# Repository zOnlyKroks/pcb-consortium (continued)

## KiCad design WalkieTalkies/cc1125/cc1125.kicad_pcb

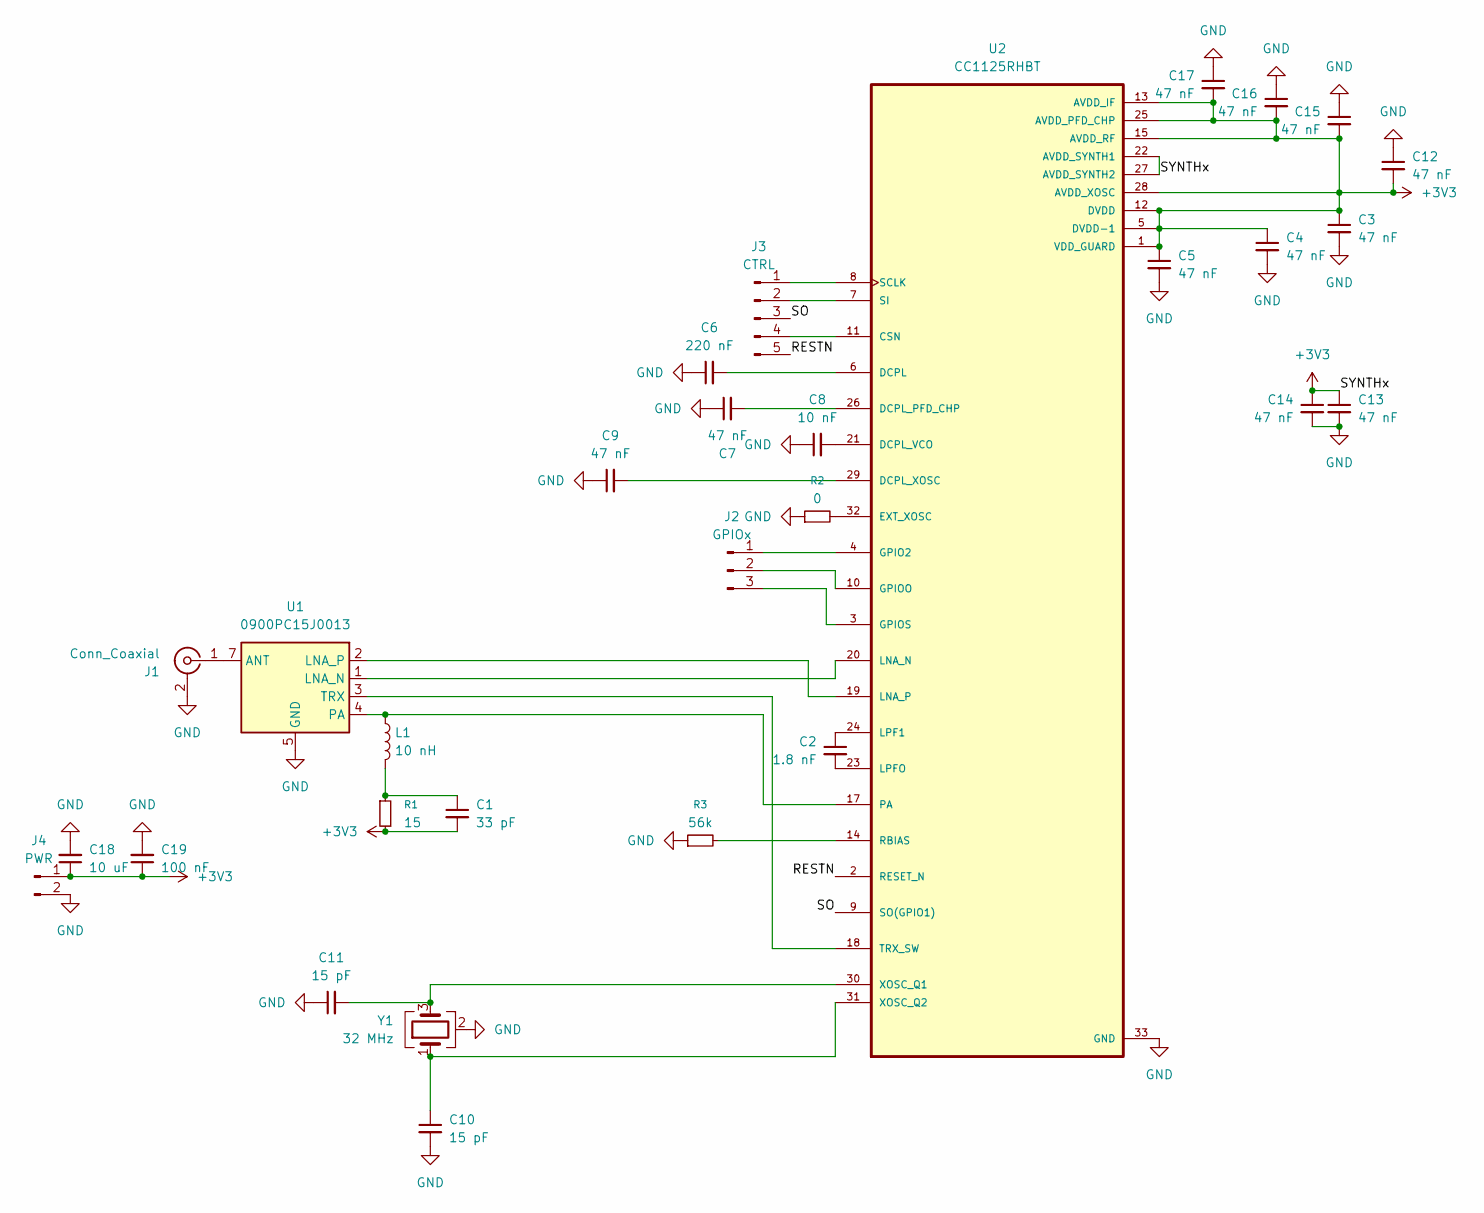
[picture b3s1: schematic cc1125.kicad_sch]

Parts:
C1: 33 pF; C_0603_1608Metric
C2: 1.8 nF; C_0603_1608Metric
C3, C4, C5, C7, C9, C12, C13, C14, C15, C16, C17: 47 nF; C_0603_1608Metric
C6: 220 nF; C_0603_1608Metric
C8: 10 nF; C_0603_1608Metric
C10, C11: 15 pF; C_0603_1608Metric
C18: 10 uF; C_0603_1608Metric
C19: 100 nF; C_0603_1608Metric
J1: Conn_Coaxial; SMA_BAT_Wireless_BWSMA-KWE-Z001
J2: GPIOx; PinHeader_1x03_P2.54mm_Vertical
J3: CTRL; PinHeader_1x05_P2.54mm_Vertical
J4: PWR; PinHeader_1x02_P2.54mm_Vertical
L1: 10 nH; L_0805_2012Metric
R1: 15; R_0603_1608Metric
R2: 0; R_0603_1608Metric
R3: 56k; R_0603_1608Metric
U1: 0900PC15J0013; Balun_Johanson_0900PC15J0013
U2: CC1125RHBT; IC_ADS125H01IRHBT
Y1: 32 MHz; Crystal_SMD_3225-4Pin_3.2x2.5mm

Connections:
+3V3: C1.2, C3.1, C4.1, C5.1, C12.2, C13.1, C14.1, C15.2, C16.2, C17.2, C18.1, C19.1, J4.1, R1.2, U2.1 (VDD_GUARD), U2.5 (DVDD-1), U2.12 (DVDD), U2.13 (AVDD_IF), U2.15 (AVDD_RF), U2.22 (AVDD_SYNTH1), U2.25 (AVDD_PFD_CHP), U2.27 (AVDD_SYNTH2), U2.28 (AVDD_XOSC)
/RESTN: J3.5, U2.2 (RESET_N)
/SO: J3.3, U2.9 (SO(GPIO1))
GND: C3.2, C4.2, C5.2, C6.1, C7.1, C8.1, C9.1, C10.2, C11.1, C12.1, C13.2, C14.2, C15.1, C16.1, C17.1, C18.2, C19.2, J1.2 (Ext), J4.2, R2.1, R3.1, U1.5 (GND), U1.6 (GND), U1.8 (GND), U1.9 (GND), U1.10 (GND), U2.33 (GND), Y1.2 (G), Y1.4 (G)
unnamed: C1.1, L1.2, R1.1
unnamed: J1.1 (In), U1.7 (ANT)
unnamed: J2.1, U2.4 (GPIO2)
unnamed: J2.2, U2.10 (GPIOO)
unnamed: J2.3, U2.3 (GPIOS)
unnamed: J3.1, U2.8 (SCLK)
unnamed: J3.2, U2.7 (SI)
unnamed: J3.4, U2.11 (CSN)
unnamed: U1.1 (LNA_N), U2.20 (LNA_N)
unnamed: U1.2 (LNA_P), U2.19 (LNA_P)
unnamed: L1.1, U1.4 (PA), U2.17 (PA)
unnamed: U1.3 (TRX), U2.18 (TRX_SW)
unnamed: C6.2, U2.6 (DCPL)
unnamed: C7.2, U2.26 (DCPL_PFD_CHP)
unnamed: C8.2, U2.21 (DCPL_VCO)
unnamed: C9.2, U2.29 (DCPL_XOSC)
unnamed: R2.2, U2.32 (EXT_XOSC)
unnamed: C2.1, U2.24 (LPF1)
unnamed: C2.2, U2.23 (LPFO)
unnamed: R3.2, U2.14 (RBIAS)
unnamed: C11.2, U2.30 (XOSC_Q1), Y1.3
unnamed: C10.1, U2.31 (XOSC_Q2), Y1.1

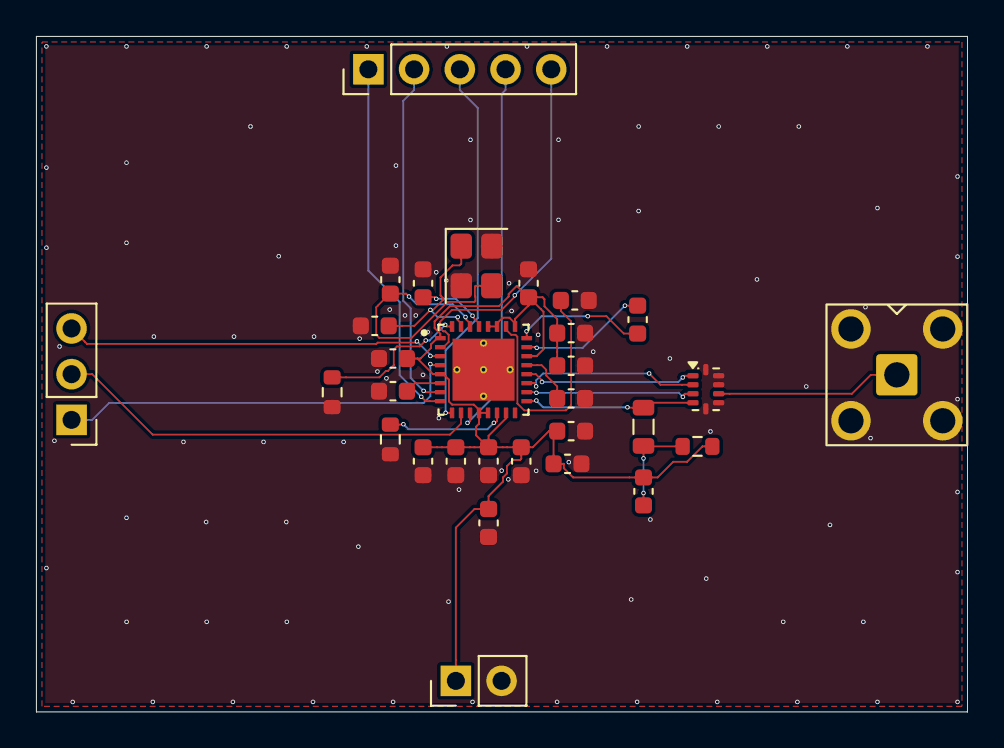
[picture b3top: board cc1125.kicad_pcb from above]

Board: 2 copper layers, 51.7 x 37.5 mm, 30 parts (0 on the bottom side), 26 nets.

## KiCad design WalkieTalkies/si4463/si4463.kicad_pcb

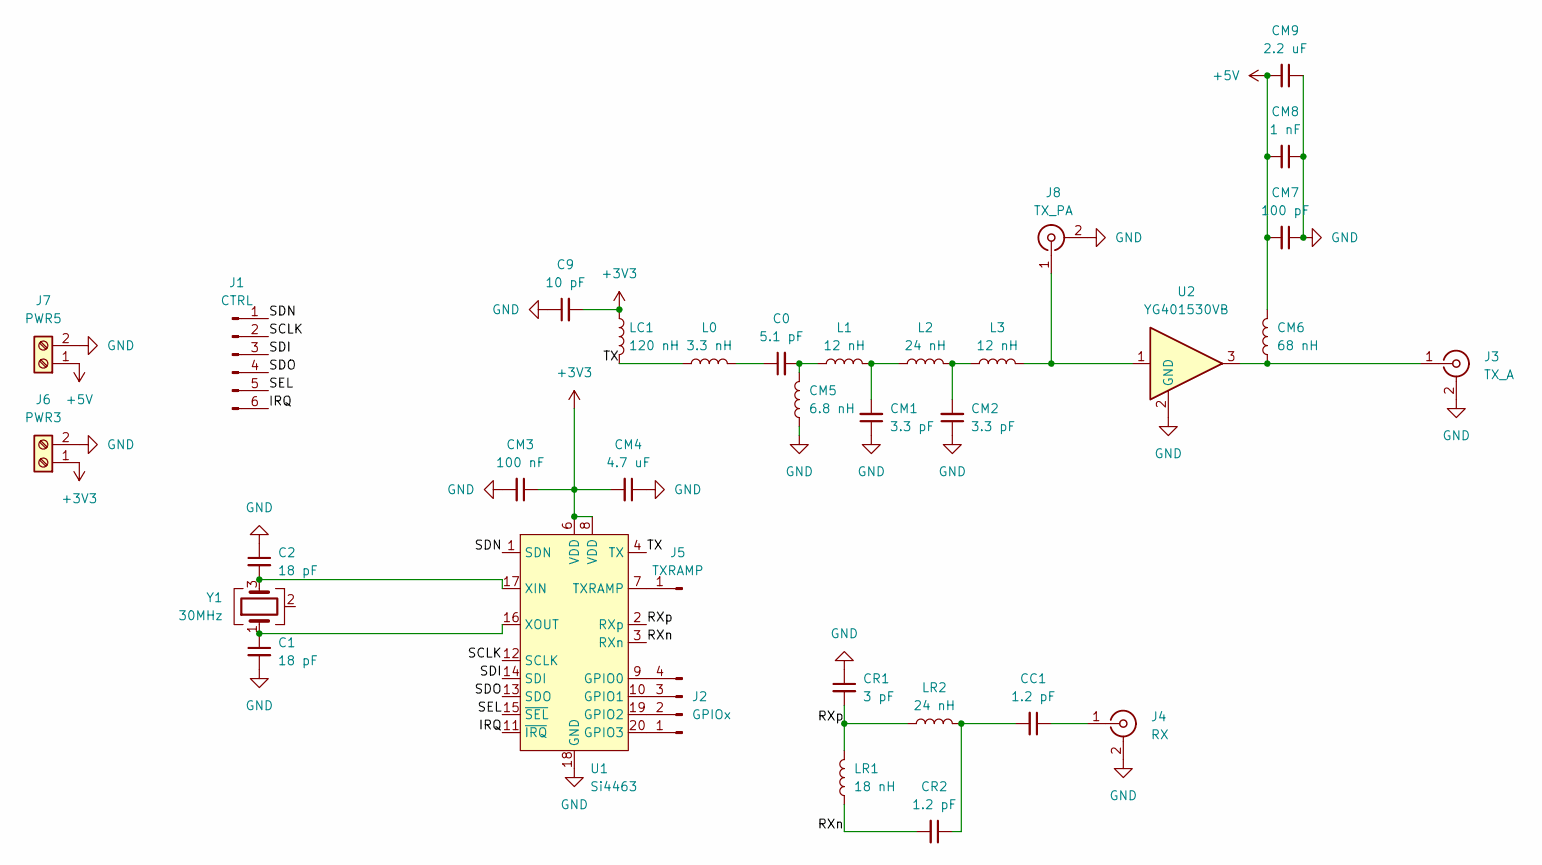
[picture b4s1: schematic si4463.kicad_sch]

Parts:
C0: 5.1 pF; C_0603_1608Metric
C1, C2: 18 pF; C_0603_1608Metric
C9: 10 pF; C_0603_1608Metric
CC1: 1.2 pF; C_0603_1608Metric
CM1, CM2: 3.3 pF; C_0603_1608Metric
CM3: 100 nF; C_0603_1608Metric
CM4: 4.7 uF; C_0603_1608Metric
CM5: 6.8 nH; L_0805_2012Metric
CM6: 68 nH; L_0805_2012Metric
CM7: 100 pF; C_0603_1608Metric
CM8: 1 nF; C_0603_1608Metric
CM9: 2.2 uF; C_0603_1608Metric
CR1: 3 pF; C_0603_1608Metric
CR2: 1.2 pF; C_0603_1608Metric
J1: CTRL; PinHeader_1x06_P2.54mm_Vertical
J2: GPIOx; PinHeader_1x04_P2.54mm_Vertical
J3: TX_A; SMA_BAT_Wireless_BWSMA-KWE-Z001
J4: RX; SMA_BAT_Wireless_BWSMA-KWE-Z001
J5: TXRAMP; PinHeader_1x01_P2.54mm_Vertical
J6: PWR3; WJ500V-5.08-2P
J7: PWR5; WJ500V-5.08-2P
J8: TX_PA; SMA_BAT_Wireless_BWSMA-KWE-Z001
L0: 3.3 nH; L_0805_2012Metric
L1, L3: 12 nH; L_0805_2012Metric
L2: 24 nH; L_0805_2012Metric
LC1: 120 nH; L_0805_2012Metric
LR1: 18 nH; L_0805_2012Metric
LR2: 24 nH; L_0805_2012Metric
U1: Si4463; QFN-20-1EP_4x4mm_P0.5mm_EP2.6x2.6mm_ThermalVias
U2: YG401530VB; SOT-89-3
Y1: 30MHz; Crystal_SMD_3225-4Pin_3.2x2.5mm

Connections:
+3V3: C9.2, CM3.1, CM4.2, J6.1, LC1.1, U1.6 (VDD), U1.8 (VDD)
+5V: CM6.2, CM7.2, CM8.2, CM9.2, J7.1
/IRQ: J1.6, U1.11 (~IRQ)
/RXn: CR2.2, LR1.1, U1.3 (RXn)
/RXp: CR1.2, LR1.2, LR2.1, U1.2 (RXp)
/SCLK: J1.2, U1.12 (SCLK)
/SDI: J1.3, U1.14 (SDI)
/SDN: J1.1, U1.1 (SDN)
/SDO: J1.4, U1.13 (SDO)
/SEL: J1.5, U1.15 (~SEL)
/TX: L0.1, LC1.2, U1.4 (TX)
GND: C1.2, C2.1, C9.1, CM1.1, CM2.1, CM3.2, CM4.1, CM5.1, CM7.1, CM8.1, CM9.1, CR1.1, J3.2 (Ext), J4.2 (Ext), J6.2, J7.2, J8.2 (Ext), U1.18 (GND), U1.21 (GND), U2.2 (GND_2)
unnamed: C0.1, L0.2
unnamed: C0.2, CM5.2, L1.1
unnamed: CC1.2, CR2.1, LR2.2
unnamed: CM1.2, L1.2, L2.1
unnamed: CM2.2, L2.2, L3.1
unnamed: J2.1, U1.20 (GPIO3)
unnamed: J2.2, U1.19 (GPIO2)
unnamed: J2.3, U1.10 (GPIO1)
unnamed: J2.4, U1.9 (GPIO0)
unnamed: CM6.1, J3.1 (In), U2.3
unnamed: CC1.1, J4.1 (In)
unnamed: J5.1 (Pin_1_1), U1.7 (TXRAMP)
unnamed: J8.1 (In), L3.2, U2.1
unnamed: C2.2, U1.17 (XIN), Y1.3
unnamed: C1.1, U1.16 (XOUT), Y1.1
unnamed: Y1.2 (G), Y1.4 (G)

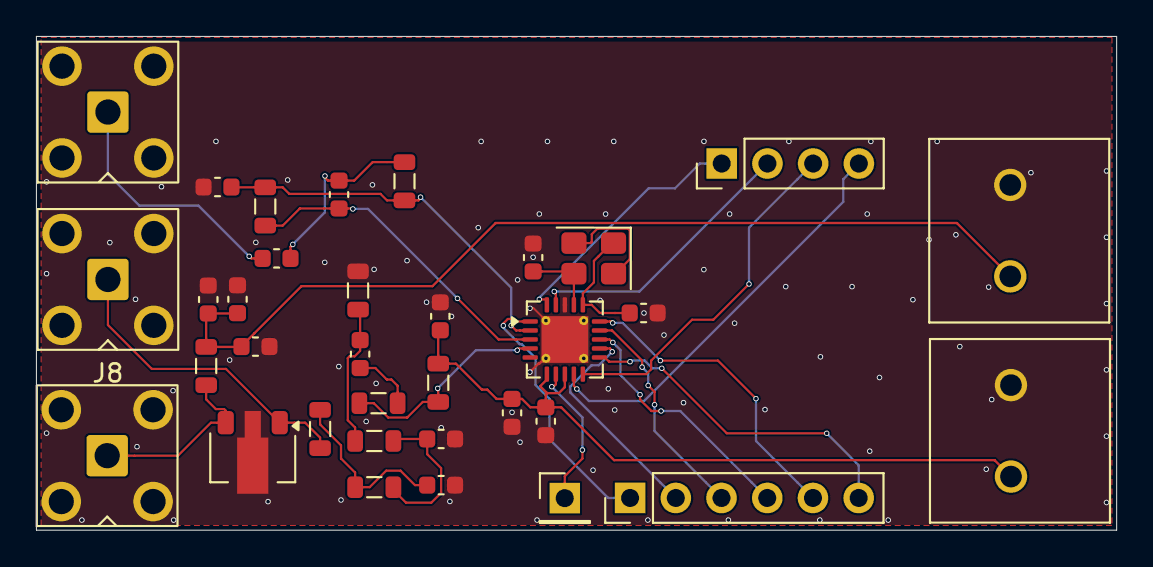
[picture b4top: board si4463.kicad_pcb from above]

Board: 2 copper layers, 60.0 x 27.4 mm, 34 parts (0 on the bottom side), 28 nets.

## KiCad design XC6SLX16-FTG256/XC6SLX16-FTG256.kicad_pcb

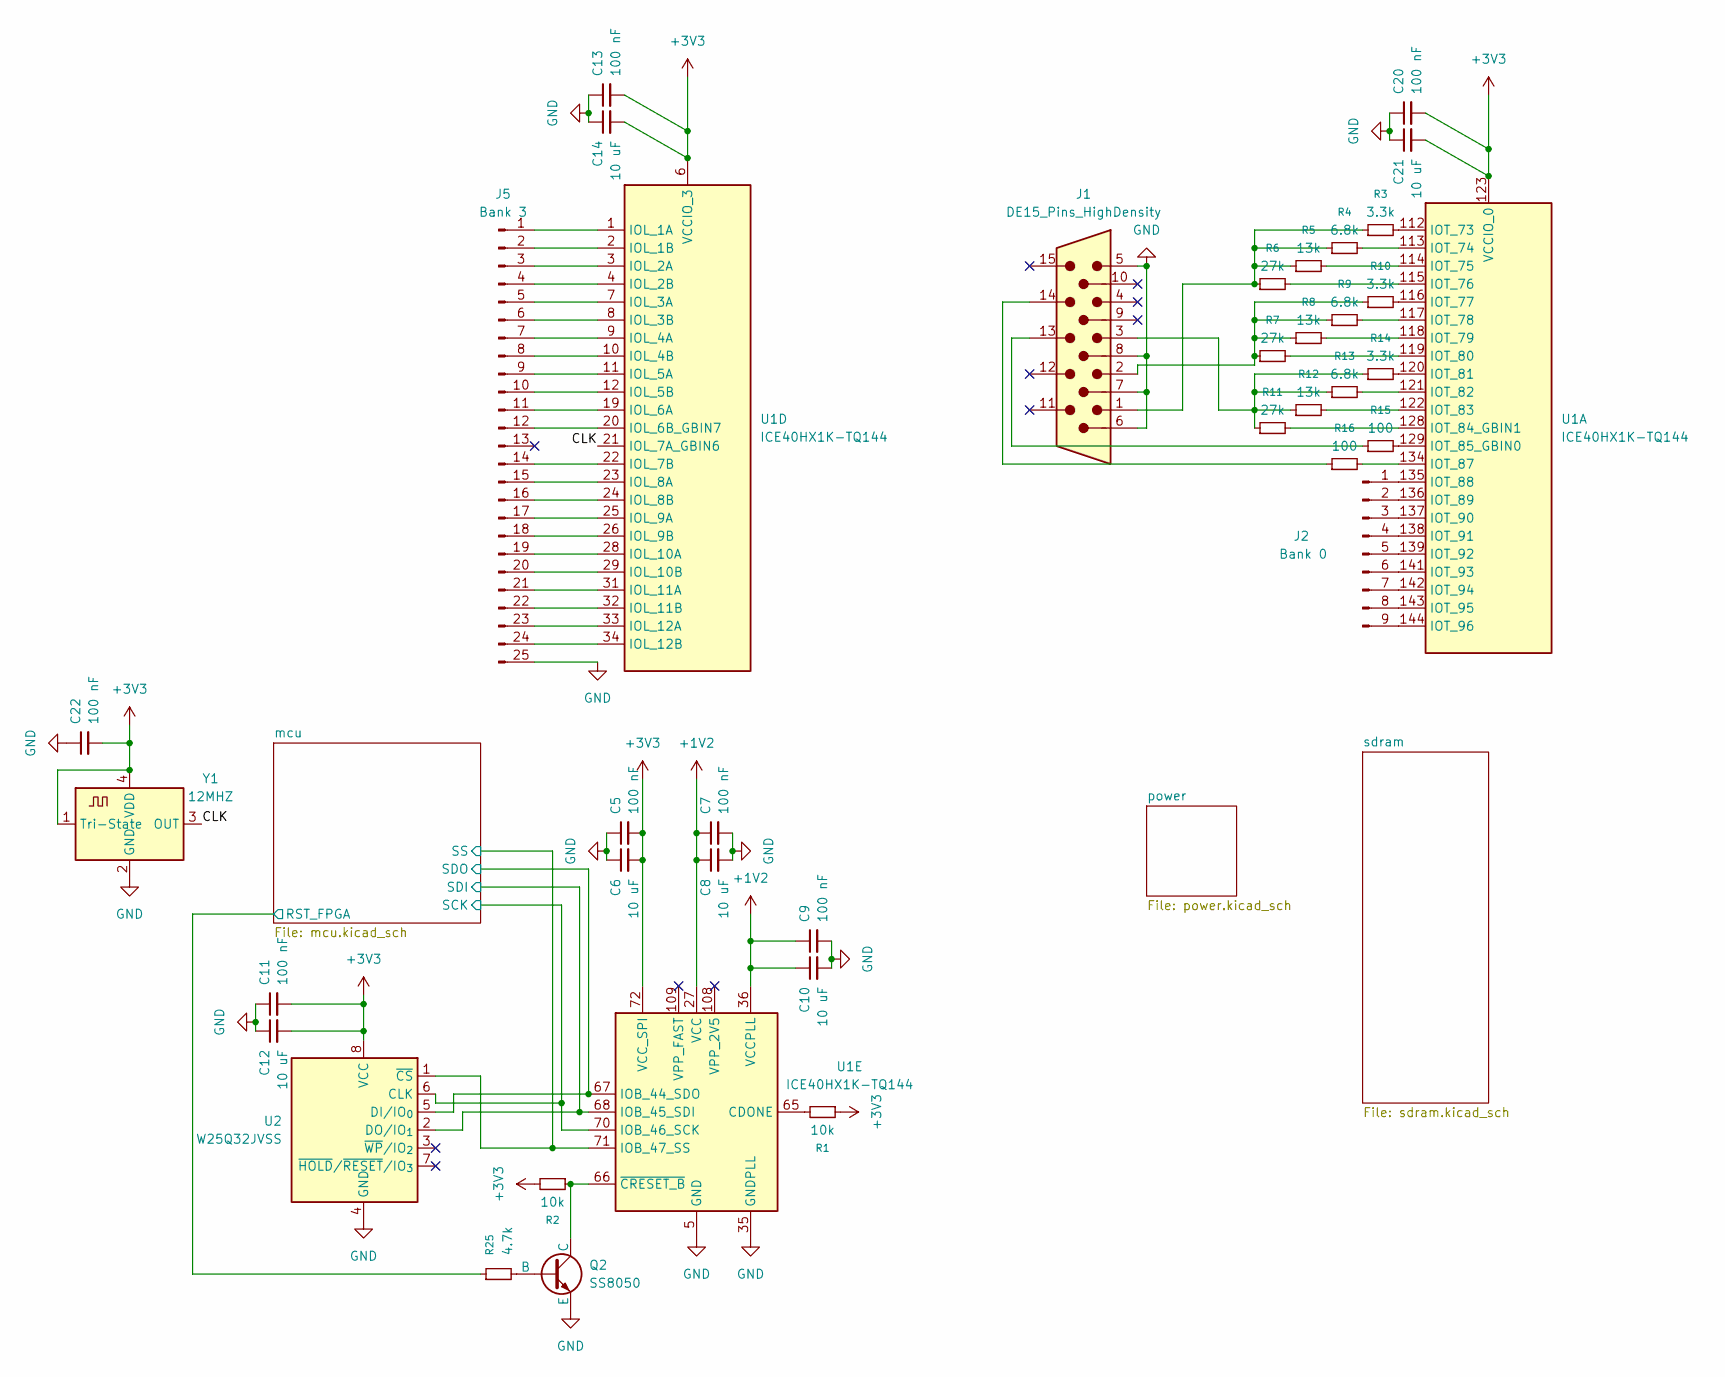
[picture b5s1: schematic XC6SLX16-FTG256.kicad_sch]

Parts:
C5, C7, C9, C11, C13, C20, C22: 100 nF; C_0603_1608Metric
C6, C8, C10, C12, C14, C21: 10 uF; C_0603_1608Metric
J1: DE15_Pins_HighDensity; DSUB-15-HD_Pins_Horizontal_P2.29x1.90mm_EdgePinOffset3.03mm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
J2: Bank 0; PinHeader_1x09_P2.54mm_Vertical
J5: Bank 3; PinHeader_1x25_P2.54mm_Vertical
Q2: SS8050; SOT-23
R1, R2: 10k; R_0603_1608Metric
R3, R10, R14: 3.3k; R_0603_1608Metric
R4, R9, R13: 6.8k; R_0603_1608Metric
R5, R8, R12: 13k; R_0603_1608Metric
R6, R7, R11: 27k; R_0603_1608Metric
R15, R16: 100; R_0603_1608Metric
R25: 4.7k; R_0603_1608Metric; LCSC Part # C23162
U1: ICE40HX1K-TQ144; TQFP-144_20x20mm_P0.5mm
U2: W25Q32JVSS; SOIC-8_5.3x5.3mm_P1.27mm
Y1: 12MHZ; Crystal_SMD_3225-4Pin_3.2x2.5mm; LCSC Part # C2901561

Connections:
+1V2: C7.1, C8.1, C9.1, C10.1, U1.27 (VCC), U1.36 (VCCPLL), U1.51 (VCC), U1.92 (VCC), U1.111 (VCC); also elsewhere on the board
+3V3: C5.2, C6.2, C11.2, C12.2, C13.2, C14.2, C20.2, C21.2, C22.2, R1.1, R2.2, U1.6 (VCCIO_3), U1.30 (VCCIO_3), U1.72 (VCC_SPI), U1.123 (VCCIO_0), U1.133 (VCCIO_0), U2.8 (VCC), Y1.1 (Tri-State), Y1.4 (VDD); also elsewhere on the board
/CLK: U1.21 (IOL_7A_GBIN6), Y1.3 (OUT)
/mcu/RST_FPGA: R25.1; also elsewhere on the board
/mcu/SCK: U1.70 (IOB_46_SCK), U2.6 (CLK); also elsewhere on the board
/mcu/SDI: U1.68 (IOB_45_SDI), U2.2 (DO/IO_{1}); also elsewhere on the board
/mcu/SDO: U1.67 (IOB_44_SDO), U2.5 (DI/IO_{0}); also elsewhere on the board
/mcu/SS: U1.71 (IOB_47_SS), U2.1 (~CS); also elsewhere on the board
GND: C5.1, C6.1, C7.2, C8.2, C9.2, C10.2, C11.1, C12.1, C13.1, C14.1, C20.1, C21.1, C22.1, J1.5, J1.6, J1.7, J1.8, J5.25, Q2.3 (E), U1.5 (GND), U1.13 (GND), U1.14 (GND), U1.35 (GNDPLL), U1.59 (GND), U1.69 (GND), U1.86 (GND), U1.103 (GND), U1.132 (GND), U1.140 (GND), U2.4 (GND), Y1.2 (GND); also elsewhere on the board
unnamed: J1.1, R3.1, R4.1, R5.1, R6.1
unnamed: J1.2, R7.1, R8.1, R9.1, R10.1
unnamed: J1.3, R11.1, R12.1, R13.1, R14.1
unnamed: J1.13, R15.1
unnamed: J1.14, R16.1
unnamed: J2.1, U1.135 (IOT_88)
unnamed: J2.2, U1.136 (IOT_89)
unnamed: J2.3, U1.137 (IOT_90)
unnamed: J2.4, U1.138 (IOT_91)
unnamed: J2.5, U1.139 (IOT_92)
unnamed: J2.6, U1.141 (IOT_93)
unnamed: J2.7, U1.142 (IOT_94)
unnamed: J2.8, U1.143 (IOT_95)
unnamed: J2.9, U1.144 (IOT_96)
unnamed: J5.1, U1.1 (IOL_1A)
unnamed: J5.2, U1.2 (IOL_1B)
unnamed: J5.3, U1.3 (IOL_2A)
unnamed: J5.4, U1.4 (IOL_2B)
unnamed: J5.5, U1.7 (IOL_3A)
unnamed: J5.6, U1.8 (IOL_3B)
unnamed: J5.7, U1.9 (IOL_4A)
unnamed: J5.8, U1.10 (IOL_4B)
unnamed: J5.9, U1.11 (IOL_5A)
unnamed: J5.10, U1.12 (IOL_5B)
unnamed: J5.11, U1.19 (IOL_6A)
unnamed: J5.12, U1.20 (IOL_6B_GBIN7)
unnamed: J5.14, U1.22 (IOL_7B)
unnamed: J5.15, U1.23 (IOL_8A)
unnamed: J5.16, U1.24 (IOL_8B)
unnamed: J5.17, U1.25 (IOL_9A)
unnamed: J5.18, U1.26 (IOL_9B)
unnamed: J5.19, U1.28 (IOL_10A)
unnamed: J5.20, U1.29 (IOL_10B)
unnamed: J5.21, U1.31 (IOL_11A)
unnamed: J5.22, U1.32 (IOL_11B)
unnamed: J5.23, U1.33 (IOL_12A)
unnamed: J5.24, U1.34 (IOL_12B)
unnamed: Q2.2 (B), R25.2
unnamed: Q2.1 (C), R2.1, U1.66 (~CRESET_B)
unnamed: R3.2, U1.112 (IOT_73)
unnamed: R4.2, U1.113 (IOT_74)
unnamed: R5.2, U1.114 (IOT_75)
unnamed: R6.2, U1.115 (IOT_76)
unnamed: R10.2, U1.116 (IOT_77)
unnamed: R9.2, U1.117 (IOT_78)
unnamed: R8.2, U1.118 (IOT_79)
unnamed: R7.2, U1.119 (IOT_80)
unnamed: R14.2, U1.120 (IOT_81)
unnamed: R13.2, U1.121 (IOT_82)
unnamed: R12.2, U1.122 (IOT_83)
unnamed: R11.2, U1.128 (IOT_84_GBIN1)
unnamed: R15.2, U1.129 (IOT_85_GBIN0)
unnamed: R16.2, U1.134 (IOT_87)
unnamed: R1.2, U1.65 (CDONE)

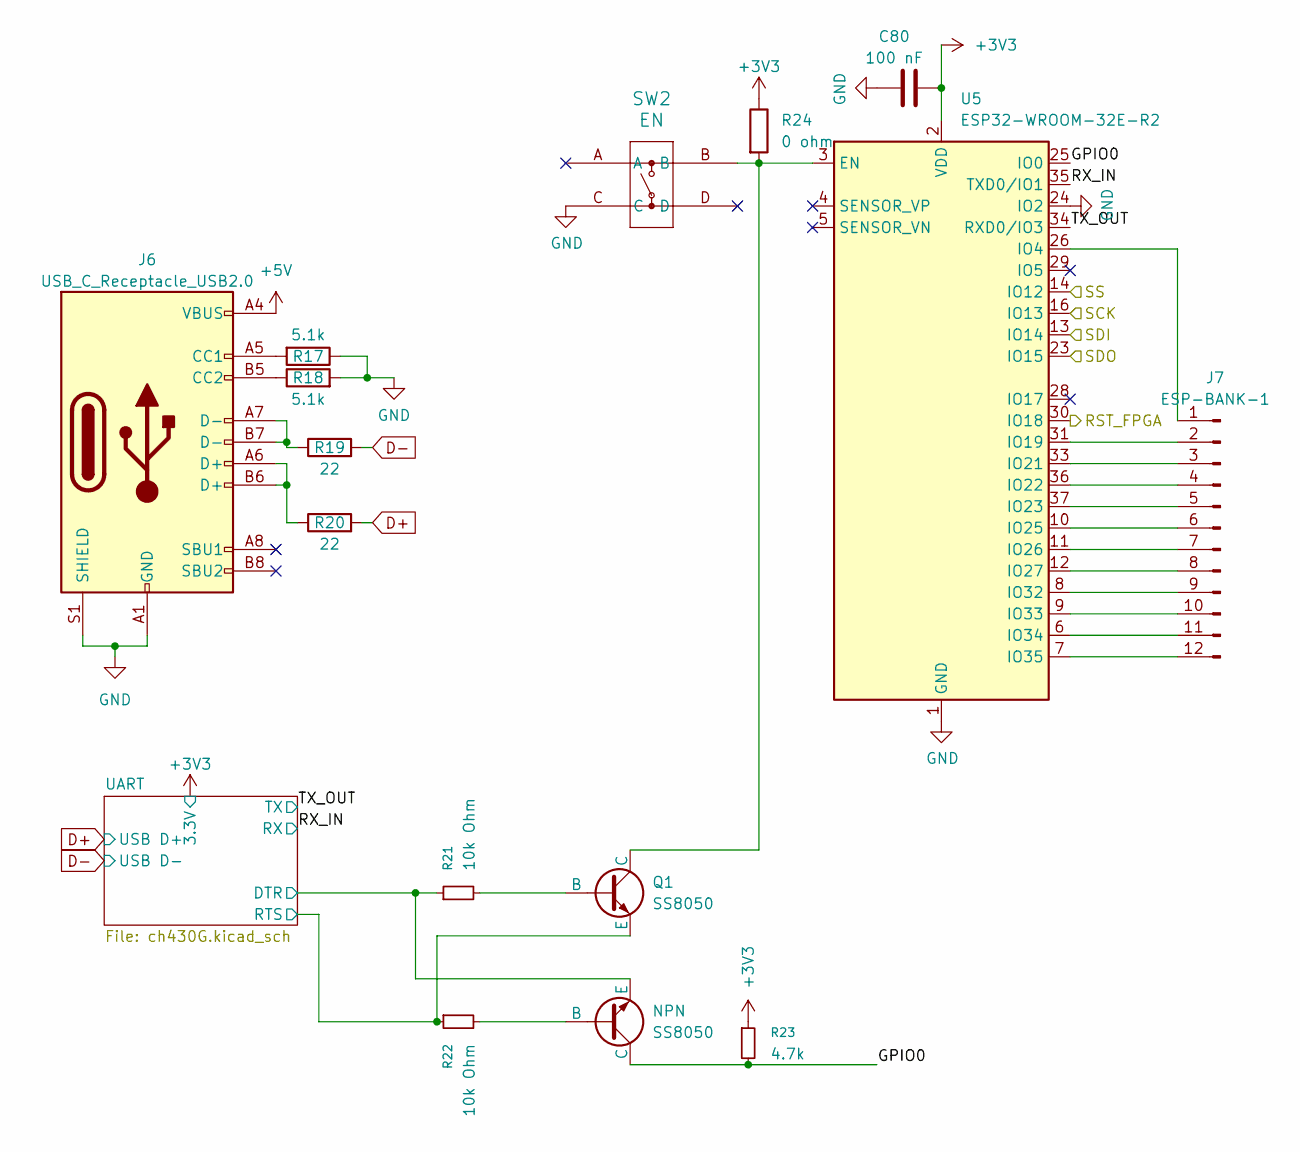
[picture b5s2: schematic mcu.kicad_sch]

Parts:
C80: 100 nF; C_0805_2012Metric; LCSC Part # C49678
J6: USB_C_Receptacle_USB2.0; USB_C_Receptacle_HRO_TYPE-C-31-M-12; JlcRotOffset 180
J7: ESP-BANK-1; PinHeader_1x12_P2.54mm_Vertical
Q1: SS8050; SOT-23
R17, R18: 5.1k; R_0805_2012Metric; LCSC Part # C27834
R19, R20: 22; R_0805_2012Metric; LCSC Part # C17561
R21, R22: 10k Ohm; R_0805_2012Metric
R23: 4.7k; R_0603_1608Metric; LCSC Part # C23162
R24: 0 ohm; R_0805_2012Metric; LCSC Part # C17477
SS8050: NPN; SOT-23
SW2: EN; KH-6X6X5H-STM_SKE; LCSC Part # C2837531
U5: ESP32-WROOM-32E-R2; ESP32-WROOM-32D

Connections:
+3V3: C80.1, R23.1, R24.1, U5.2 (VDD); also elsewhere on the board
+5V: J6.A4 (VBUS), J6.A9 (VBUS), J6.B4 (VBUS), J6.B9 (VBUS); also elsewhere on the board
/mcu/GPIO0: R23.2, SS8050.1 (C), U5.25 (IO0)
/mcu/RST_FPGA: U5.30 (IO18); also elsewhere on the board
/mcu/RX_IN: U5.35 (TXD0/IO1); also elsewhere on the board
/mcu/SCK: U5.16 (IO13); also elsewhere on the board
/mcu/SDI: U5.13 (IO14); also elsewhere on the board
/mcu/SDO: U5.23 (IO15); also elsewhere on the board
/mcu/SS: U5.14 (IO12); also elsewhere on the board
/mcu/TX_OUT: U5.34 (RXD0/IO3); also elsewhere on the board
/mcu/UART/DTR: R21.1, SS8050.3 (E); also elsewhere on the board
/mcu/UART/RTS: Q1.3 (E), R22.1; also elsewhere on the board
D+: R20.2; also elsewhere on the board
D-: R19.2; also elsewhere on the board
GND: C80.2, J6.A1 (GND), J6.A12 (GND), J6.B1 (GND), J6.B12 (GND), J6.S1 (SHIELD), R17.1, R18.2, SW2.C, U5.1 (GND), U5.15 (GND), U5.24 (IO2), U5.38 (GND), U5.39 (GND); also elsewhere on the board
unnamed: J6.A5 (CC1), R17.2
unnamed: J6.B5 (CC2), R18.1
unnamed: J6.A6 (D+), J6.B6 (D+), R20.1
unnamed: J6.A7 (D-), J6.B7 (D-), R19.1
unnamed: J7.1, U5.26 (IO4)
unnamed: J7.2, U5.31 (IO19)
unnamed: J7.3, U5.33 (IO21)
unnamed: J7.4, U5.36 (IO22)
unnamed: J7.5, U5.37 (IO23)
unnamed: J7.6, U5.10 (IO25)
unnamed: J7.7, U5.11 (IO26)
unnamed: J7.8, U5.12 (IO27)
unnamed: J7.9, U5.8 (IO32)
unnamed: J7.10, U5.9 (IO33)
unnamed: J7.11, U5.6 (IO34)
unnamed: J7.12, U5.7 (IO35)
unnamed: Q1.2 (B), R21.2
unnamed: Q1.1 (C), R24.2, SW2.B, U5.3 (EN)
unnamed: R22.2, SS8050.2 (B)

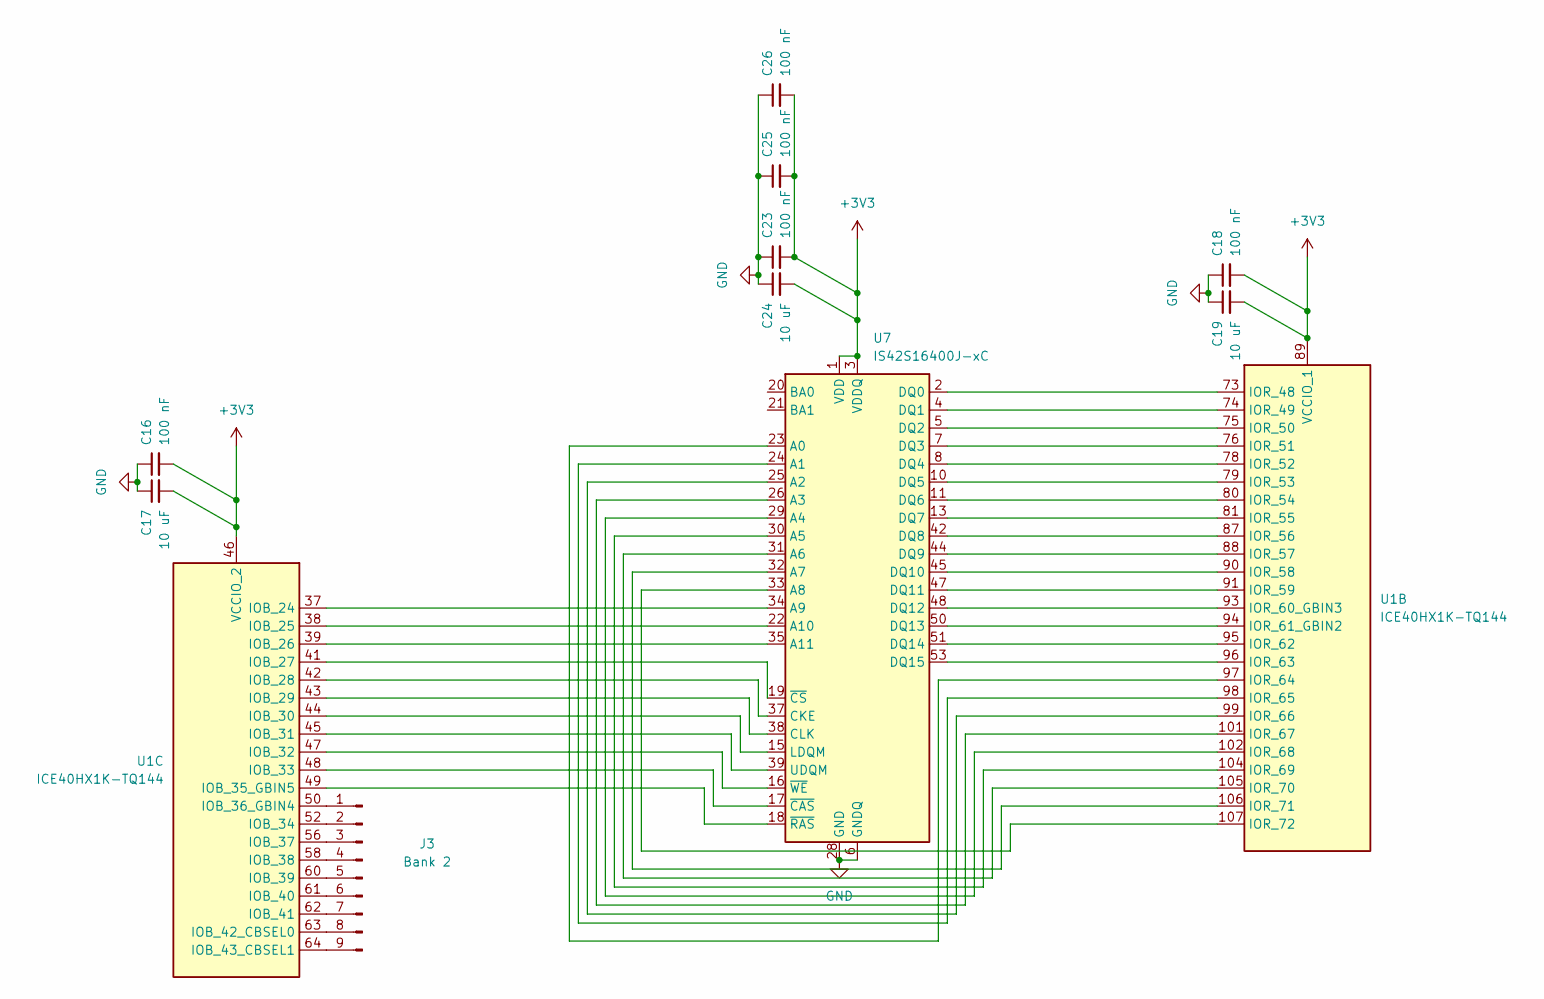
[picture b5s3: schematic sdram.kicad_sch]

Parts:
C16, C18, C23, C25, C26: 100 nF; C_0603_1608Metric
C17, C19, C24: 10 uF; C_0603_1608Metric
J3: Bank 2; PinHeader_1x09_P2.54mm_Vertical
U1: ICE40HX1K-TQ144; TQFP-144_20x20mm_P0.5mm
U7: IS42S16400J-xC; TSOP-II-54_22.2x10.16mm_P0.8mm

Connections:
+3V3: C16.2, C17.2, C18.2, C19.2, C23.2, C24.2, C25.2, C26.2, U1.46 (VCCIO_2), U1.57 (VCCIO_2), U1.89 (VCCIO_1), U1.100 (VCCIO_1), U7.1 (VDD), U7.3 (VDDQ), U7.9 (VDDQ), U7.14 (VDD), U7.27 (VDD), U7.43 (VDDQ), U7.49 (VDDQ); also elsewhere on the board
GND: C16.1, C17.1, C18.1, C19.1, C23.1, C24.1, C25.1, C26.1, U7.6 (GNDQ), U7.12 (GNDQ), U7.28 (GND), U7.41 (GND), U7.46 (GNDQ), U7.52 (GNDQ), U7.54 (GND); also elsewhere on the board
unnamed: J3.1, U1.50 (IOB_36_GBIN4)
unnamed: J3.2, U1.52 (IOB_34)
unnamed: J3.3, U1.56 (IOB_37)
unnamed: J3.4, U1.58 (IOB_38)
unnamed: J3.5, U1.60 (IOB_39)
unnamed: J3.6, U1.61 (IOB_40)
unnamed: J3.7, U1.62 (IOB_41)
unnamed: J3.8, U1.63 (IOB_42_CBSEL0)
unnamed: J3.9, U1.64 (IOB_43_CBSEL1)
unnamed: U1.73 (IOR_48), U7.2 (DQ0)
unnamed: U1.74 (IOR_49), U7.4 (DQ1)
unnamed: U1.75 (IOR_50), U7.5 (DQ2)
unnamed: U1.76 (IOR_51), U7.7 (DQ3)
unnamed: U1.78 (IOR_52), U7.8 (DQ4)
unnamed: U1.79 (IOR_53), U7.10 (DQ5)
unnamed: U1.80 (IOR_54), U7.11 (DQ6)
unnamed: U1.81 (IOR_55), U7.13 (DQ7)
unnamed: U1.87 (IOR_56), U7.42 (DQ8)
unnamed: U1.88 (IOR_57), U7.44 (DQ9)
unnamed: U1.90 (IOR_58), U7.45 (DQ10)
unnamed: U1.91 (IOR_59), U7.47 (DQ11)
unnamed: U1.93 (IOR_60_GBIN3), U7.48 (DQ12)
unnamed: U1.94 (IOR_61_GBIN2), U7.50 (DQ13)
unnamed: U1.95 (IOR_62), U7.51 (DQ14)
unnamed: U1.96 (IOR_63), U7.53 (DQ15)
unnamed: U1.97 (IOR_64), U7.23 (A0)
unnamed: U1.98 (IOR_65), U7.24 (A1)
unnamed: U1.99 (IOR_66), U7.25 (A2)
unnamed: U1.101 (IOR_67), U7.26 (A3)
unnamed: U1.102 (IOR_68), U7.29 (A4)
unnamed: U1.104 (IOR_69), U7.30 (A5)
unnamed: U1.105 (IOR_70), U7.31 (A6)
unnamed: U1.106 (IOR_71), U7.32 (A7)
unnamed: U1.107 (IOR_72), U7.33 (A8)
unnamed: U1.37 (IOB_24), U7.34 (A9)
unnamed: U1.38 (IOB_25), U7.22 (A10)
unnamed: U1.39 (IOB_26), U7.35 (A11)
unnamed: U1.41 (IOB_27), U7.19 (~CS)
unnamed: U1.42 (IOB_28), U7.37 (CKE)
unnamed: U1.43 (IOB_29), U7.38 (CLK)
unnamed: U1.44 (IOB_30), U7.15 (LDQM)
unnamed: U1.45 (IOB_31), U7.39 (UDQM)
unnamed: U1.47 (IOB_32), U7.16 (~WE)
unnamed: U1.48 (IOB_33), U7.17 (~CAS)
unnamed: U1.49 (IOB_35_GBIN5), U7.18 (~RAS)

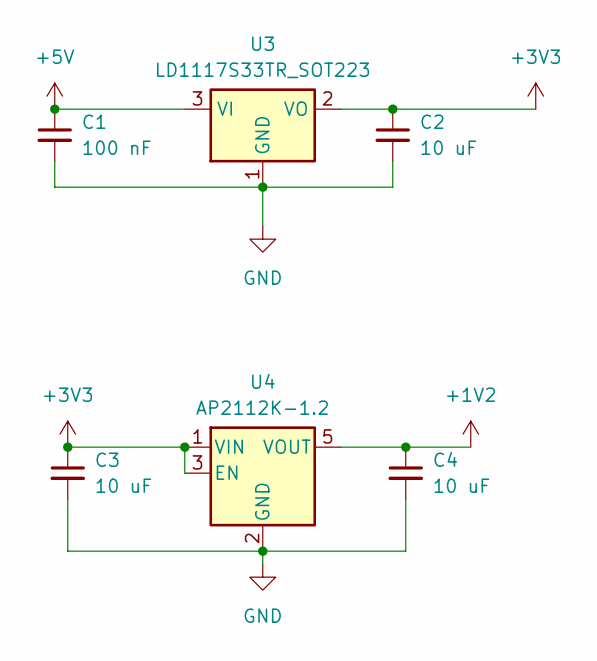
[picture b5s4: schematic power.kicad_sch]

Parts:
C1: 100 nF; C_0603_1608Metric
C2, C3, C4: 10 uF; C_0603_1608Metric
U3: LD1117S33TR_SOT223; SOT-223-3_TabPin2
U4: AP2112K-1.2; SOT-23-5

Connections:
+1V2: C4.1, U4.5 (VOUT); also elsewhere on the board
+3V3: C2.1, C3.1, U3.2 (VO), U4.1 (VIN), U4.3 (EN); also elsewhere on the board
+5V: C1.1, U3.3 (VI); also elsewhere on the board
GND: C1.2, C2.2, C3.2, C4.2, U3.1 (GND), U4.2 (GND); also elsewhere on the board

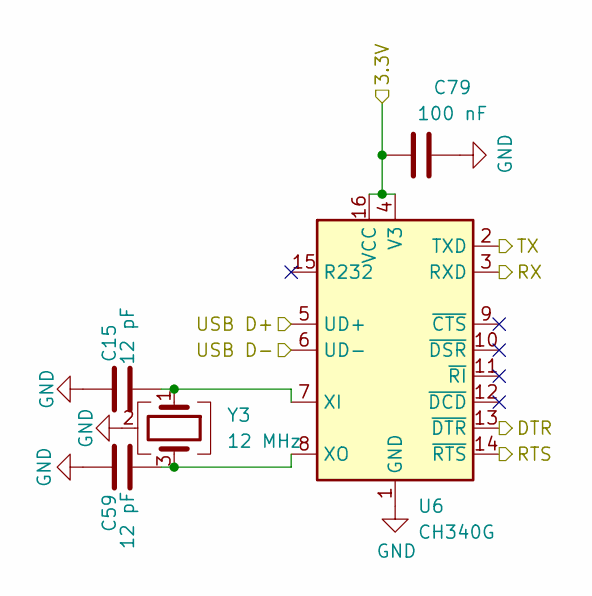
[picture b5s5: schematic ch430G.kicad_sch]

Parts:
C15, C59: 12 pF; C_0805_2012Metric; LCSC Part # C107108
C79: 100 nF; C_0805_2012Metric; LCSC Part # C49678
U6: CH340G; SOIC-16_3.9x9.9mm_P1.27mm
Y3: 12 MHz; Crystal_SMD_3225-4Pin_3.2x2.5mm; LCSC Part # C19631429

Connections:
+3V3: C79.2, U6.4 (V3), U6.16 (VCC); also elsewhere on the board
/mcu/RX_IN: U6.3 (RXD); also elsewhere on the board
/mcu/TX_OUT: U6.2 (TXD); also elsewhere on the board
/mcu/UART/DTR: U6.13 (~DTR); also elsewhere on the board
/mcu/UART/RTS: U6.14 (~RTS); also elsewhere on the board
D+: U6.5 (UD+); also elsewhere on the board
D-: U6.6 (UD-); also elsewhere on the board
GND: C15.1, C59.1, C79.1, U6.1 (GND), Y3.2 (G), Y3.4 (G); also elsewhere on the board
unnamed: C15.2, U6.7 (XI), Y3.1
unnamed: C59.2, U6.8 (XO), Y3.3

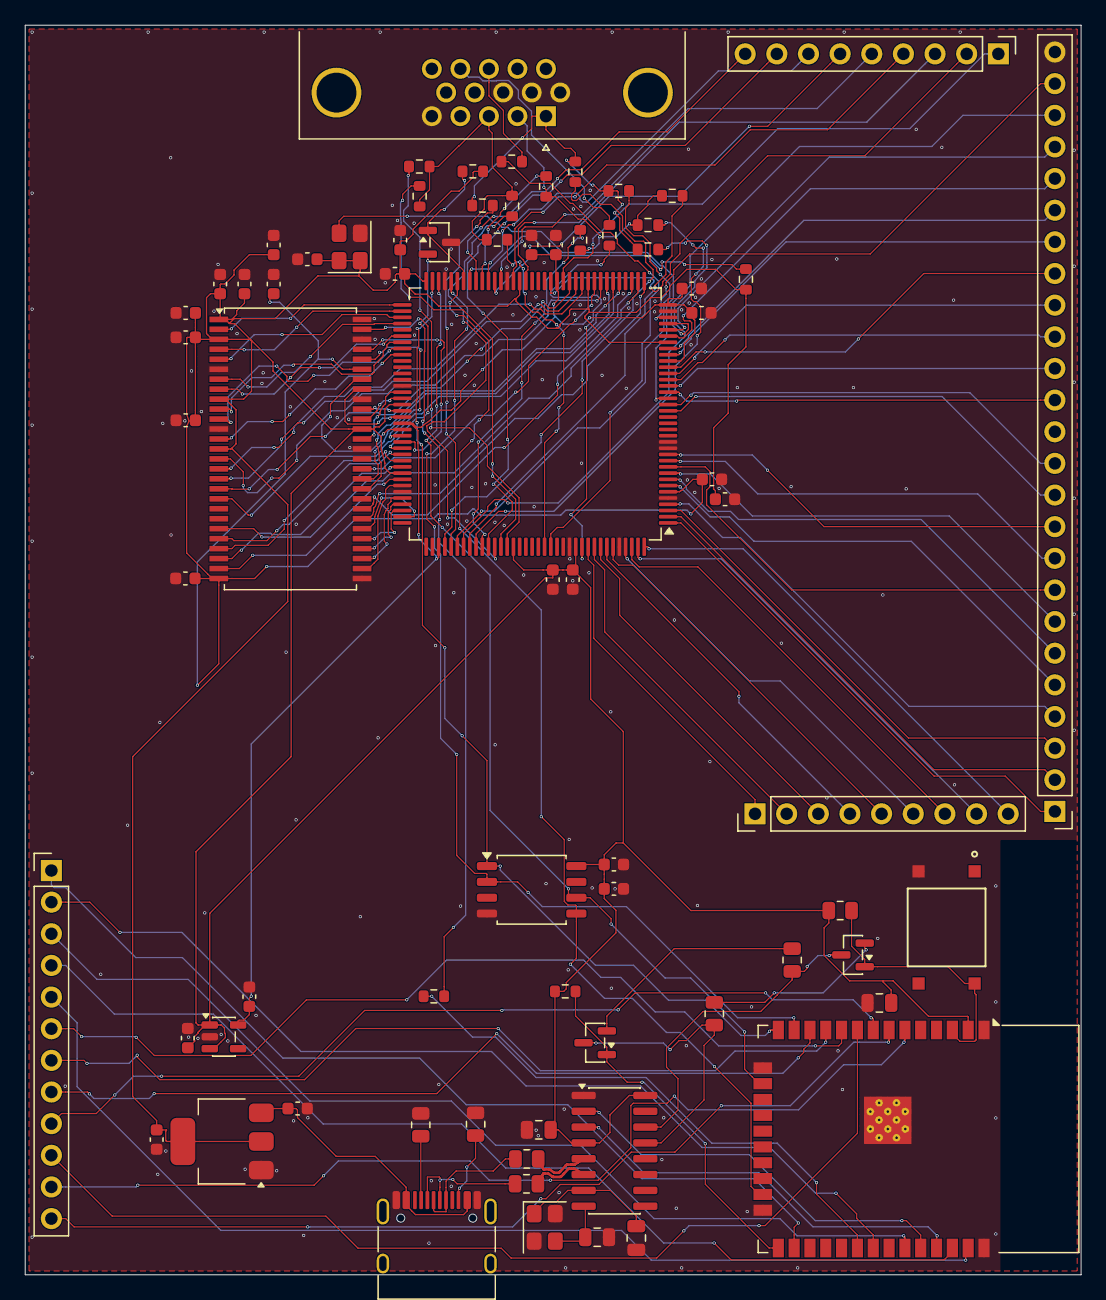
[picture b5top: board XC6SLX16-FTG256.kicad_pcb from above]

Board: 2 copper layers, 84.8 x 100.3 mm, 73 parts (0 on the bottom side), 137 nets.
